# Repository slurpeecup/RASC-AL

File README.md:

#### RASC-AL 2024: Lunar Prospecting Rover
#### TEAM RASC-GULLS

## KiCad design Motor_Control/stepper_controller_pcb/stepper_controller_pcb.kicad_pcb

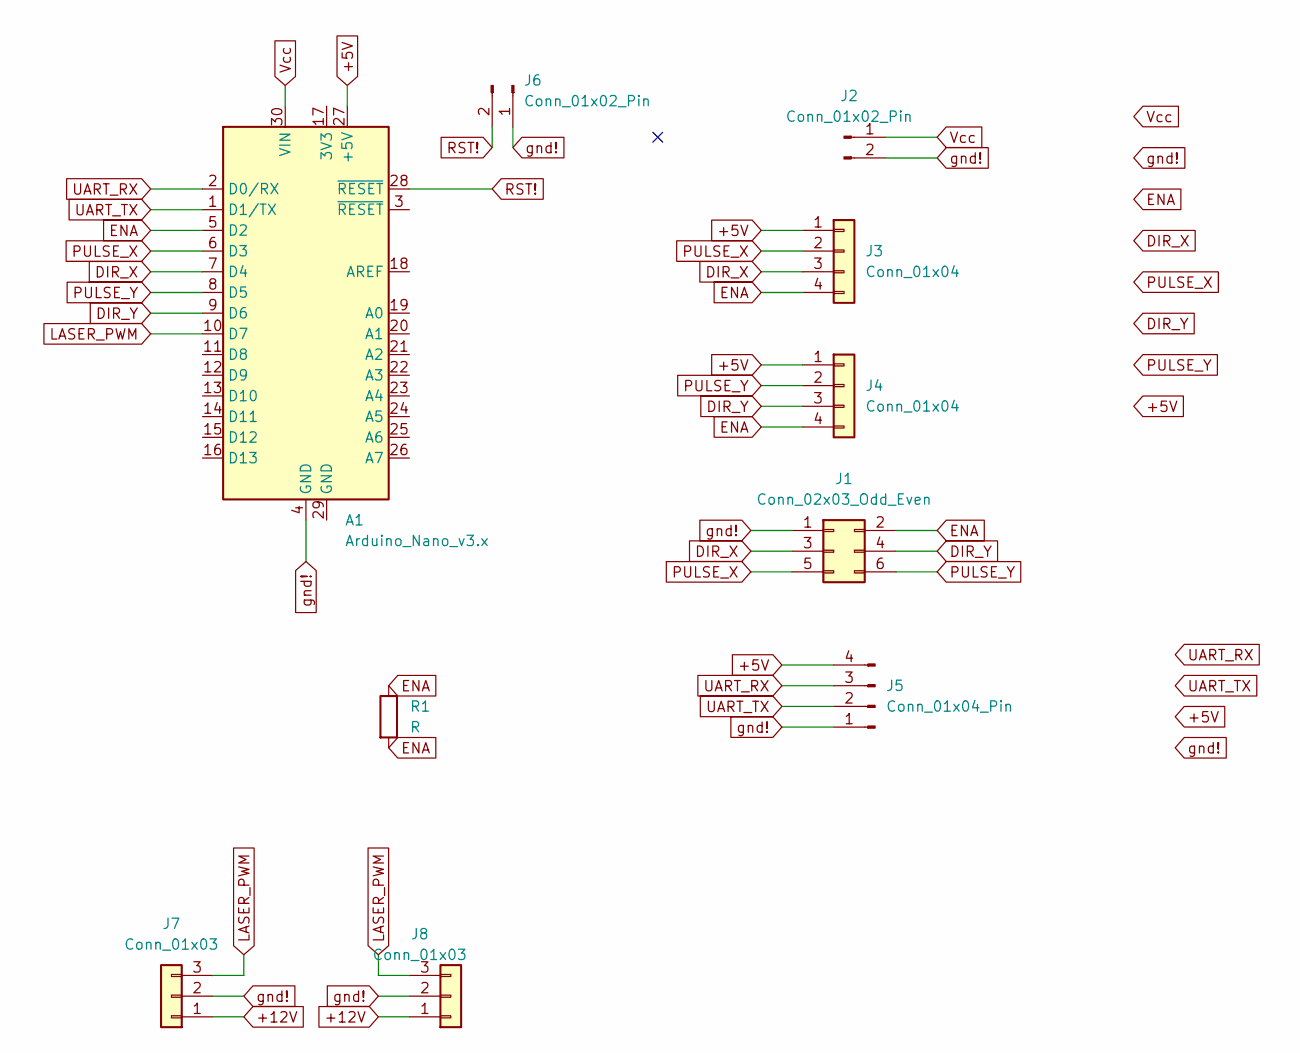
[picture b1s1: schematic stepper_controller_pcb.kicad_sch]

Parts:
A1: Arduino_Nano_v3.x; Arduino_Nano
J1: Conn_02x03_Odd_Even; PinHeader_2x03_P2.54mm_Vertical
J2: Conn_01x02_Pin; JST_XH_B2B-XH-A_1x02_P2.50mm_Vertical
J3, J4: Conn_01x04; JST_XH_B4B-XH-A_1x04_P2.50mm_Vertical
J5: Conn_01x04_Pin; PinHeader_1x04_P2.54mm_Vertical
J6: Conn_01x02_Pin; PinHeader_1x02_P2.54mm_Vertical
J7, J8: Conn_01x03; JST_XH_B3B-XH-A_1x03_P2.50mm_Vertical
R1: R

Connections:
+5V: A1.27 (+5V), J3.1, J4.1, J5.4
+12V: J7.1, J8.1
DIR_X: A1.7 (D4), J1.3, J3.3
DIR_Y: A1.9 (D6), J1.4, J4.3
ENA: A1.5 (D2), J1.2, J3.4, J4.4, R1.1, R1.2
LASER_PWM: A1.10 (D7), J7.3, J8.3
PULSE_X: A1.6 (D3), J1.5, J3.2
PULSE_Y: A1.8 (D5), J1.6, J4.2
RST!: A1.28 (~RESET), J6.2
UART_RX: A1.2 (D0/RX), J5.3
UART_TX: A1.1 (D1/TX), J5.2
Vcc: A1.30 (VIN), J2.1
gnd!: A1.4 (GND), J1.1, J2.2, J5.1, J6.1, J7.2, J8.2

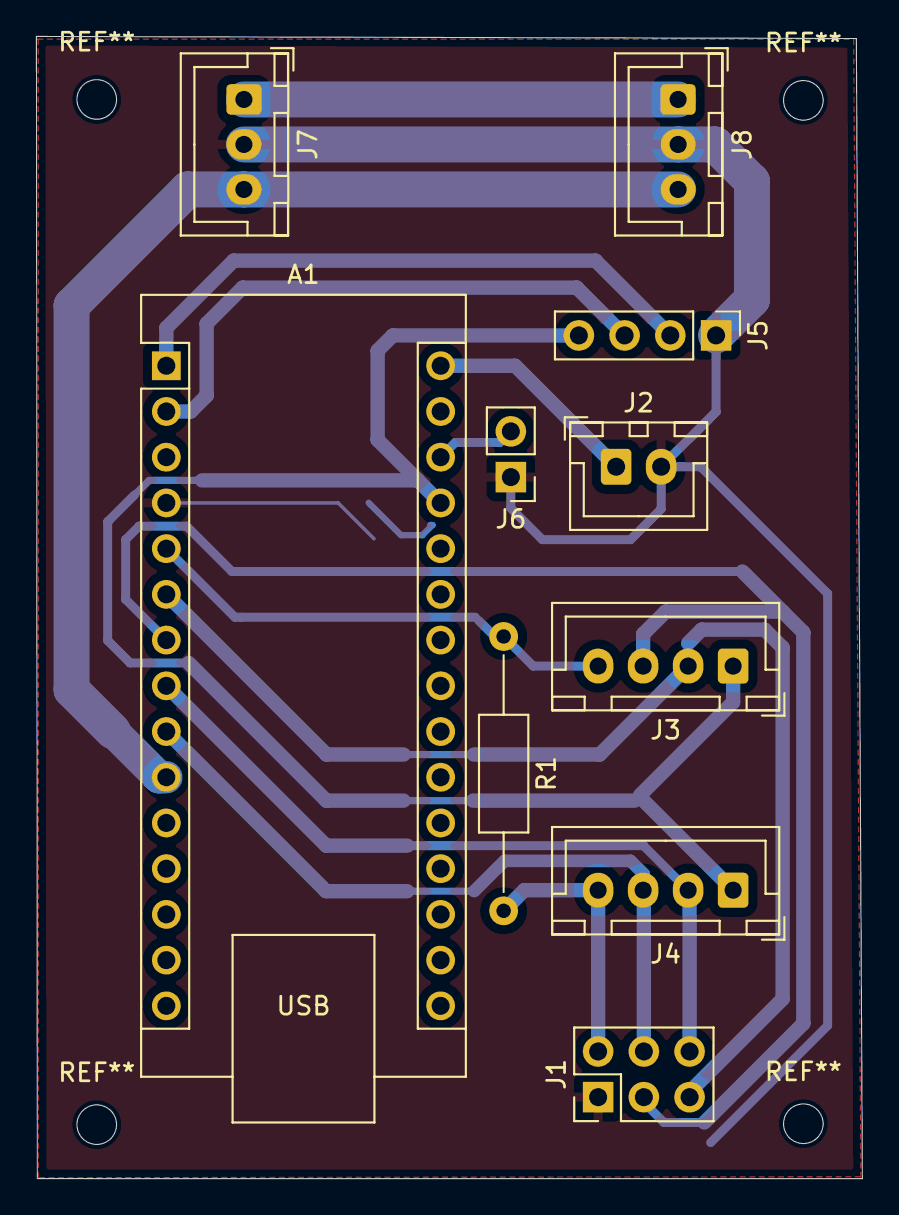
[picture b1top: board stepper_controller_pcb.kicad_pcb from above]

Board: 2 copper layers, 45.9 x 63.5 mm, 10 parts (0 on the bottom side), 13 nets.

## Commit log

2023-10-09 ~Hello Moon!
2023-10-10 now with 30% more formatting for every dollar
2023-10-10 30% more markdown per mark
2023-10-10 snippit
2023-10-10 30% more foo per bar
    Added some additional useful information regarding bash scripting.
2023-10-11 organizing
2023-10-11 organization
2023-10-12 install and install and install and install and...
2023-10-13 blah
2023-10-13 blorg
2023-10-13 image confirmation
2023-10-13 experiment
2023-10-13 logl
2023-10-13 conflicts
2023-10-13 99 conflicts and RASC-AL is... one of em actually
2023-10-13 more setup
2023-10-13 more
2023-10-16 gorbl
2023-10-16 shabl
2023-10-17 command list
2023-10-17 command list2
2023-10-17 quick test
2023-10-17 Git doc 1.0 done!
2023-10-17 CLI doc revision!
2023-10-18 CLI revisions 1.1
2023-10-19 formatting & semantic corrections
2023-10-28 more info
2023-11-11 Added HI.md
2023-11-11 gonkrete
2023-11-12 Added file
    This is phase 1 of servo motor control. This simply controls two LEDs that are given as 30% and 70% duty cycle.
2023-11-12 Rename main.c to Phase_1_LED_PWM.c
2023-11-25 LED PWM Phase 2
    This second phase has two LEDs that alternate in brightness at the press of a button. When one LED brightens up, the other dims down. These represent the two servos tilting in a longitude direction. 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
2023-11-25 Rename main.c to LED_PWM_Phase_2
    Updated title
2023-11-25 Rename LED_PWM_Phase_2 to LED_PWM_Phase_2.c
2023-11-25 Update LED_PWM_Phase_2.c
    A lot of code clean up.
2023-11-25 Rename Phase_1_LED_PWM.c to LED_PWM_Phase_1.c
    Updated title
2023-11-25 Add new file upload
2023-11-25 Update LED_PWM_Phase_2.c
    Code tidy up
2023-11-25 fun motor control stuff added, remember to pull!
2023-11-25 gitignore
2023-11-25 gorkl
2023-11-25 remember to pull!
2023-11-27 laser switch
2023-12-04 laser tweak
2024-01-26 Added stepper motor control code
2024-01-30 Updated but still rudimentary
2024-01-30 Updated code
2024-02-01 Stepper Motor Control
    This should be it in terms of controlling two steppers. Testing required.
2024-02-02 Syntax Changes
    Updated for syntax and clarity.
2024-02-07 Working code for two steppers
2024-02-07 Polished code
    Still need to add parsing functionality
2024-02-07 Documentation update
    Added proper commenting to the code for documentation and clarity.
2024-02-14 Create Automated_Stepper
    Updated stepper controls
2024-02-14 Update Automated_Stepper
2024-02-14 Create auto_step
2024-02-14 New file
    This still needs a lot of work. I was able to code the parse string information but I need to integrate it with the old.
2024-02-14 Refined code
    This is the final code. It's updated for syntax and clarity.
2024-02-16 parsley
2024-02-16 cleaned up
2024-02-16 cleaning party
2024-02-16 who needs more than 65535 steps?
2024-02-16 who needs more than 65536 steps?
2024-02-16 "Who needs 65536 steps?"
2024-02-16 readme
2024-02-16 Who could EVER need more than 65536 steps???
2024-03-08 two axis parsing
2024-03-26 hey alec pls look
2024-04-23 motor controller finally pushed up after months of idle
2024-04-27 autotracker works
2024-04-27 cleaner
2024-04-28 Create LICENSE
2024-05-04 tweaks
